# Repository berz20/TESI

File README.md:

# NV Center vectorial magnetometry Analysis

<br />

Git repository for ODMR data analysis done with confocal microscope, applied on NV centers.

<br />

# Contents

- [**How to start**](#contacts)
- [**Brief description**](#course-program)

<br />
<!--------------------------------------------------------------------->

# How to start

In order to make fitting usable, due to the necessity of using lorentzians functions with negative area, the lmfit.models and lmfit.lineshapes files have been modified adding
invlorentzian to lineshapes and the class InvLorentzianModel to models. Surely this is not an elegant neither smart way to do it, but is the only one that has worked stably.

- Search for the files that should be in your python3.10/site-packages/lmfit (on Linux it's sited in ~/.local/lib)
- Either copy the two files for github repository/startup or modify them by adding the modules (Reccomended way)

<br />
<!--------------------------------------------------------------------->

# Brief description

Directories (really messy):

- data
  - Contains data from lab experiences, dir ODMR contains all sets
- docs
  - Abstract and some useful pdfs
- output
  - Contains all txt files filled with the printed output of every run and in dir img all the images created with file src/find_peak_final.py
- presentation
  - Contains all svg files created with Inkscape and slides
- src_EB
  - variables.py : self explanatory
  - functions.py : self explanatory
  - fit_peak_final.py : find peaks, fits with a InvLorentzianModel (with few changes could be implemented for using Gaussians, Lorentzians and Voigt)
  - test_rotative_vectors.py : (only for 8 peaks spectrums) find peaks, fits, plots multiple, plots peaks points and fits with model from hamiltonians.py evaluating possible angle for axis
  - multiple_vector.py : same left graph but 3d plotting of possible vectors
- usb
  - data from lab
  <br />
  <!--------------------------------------------------------------------->

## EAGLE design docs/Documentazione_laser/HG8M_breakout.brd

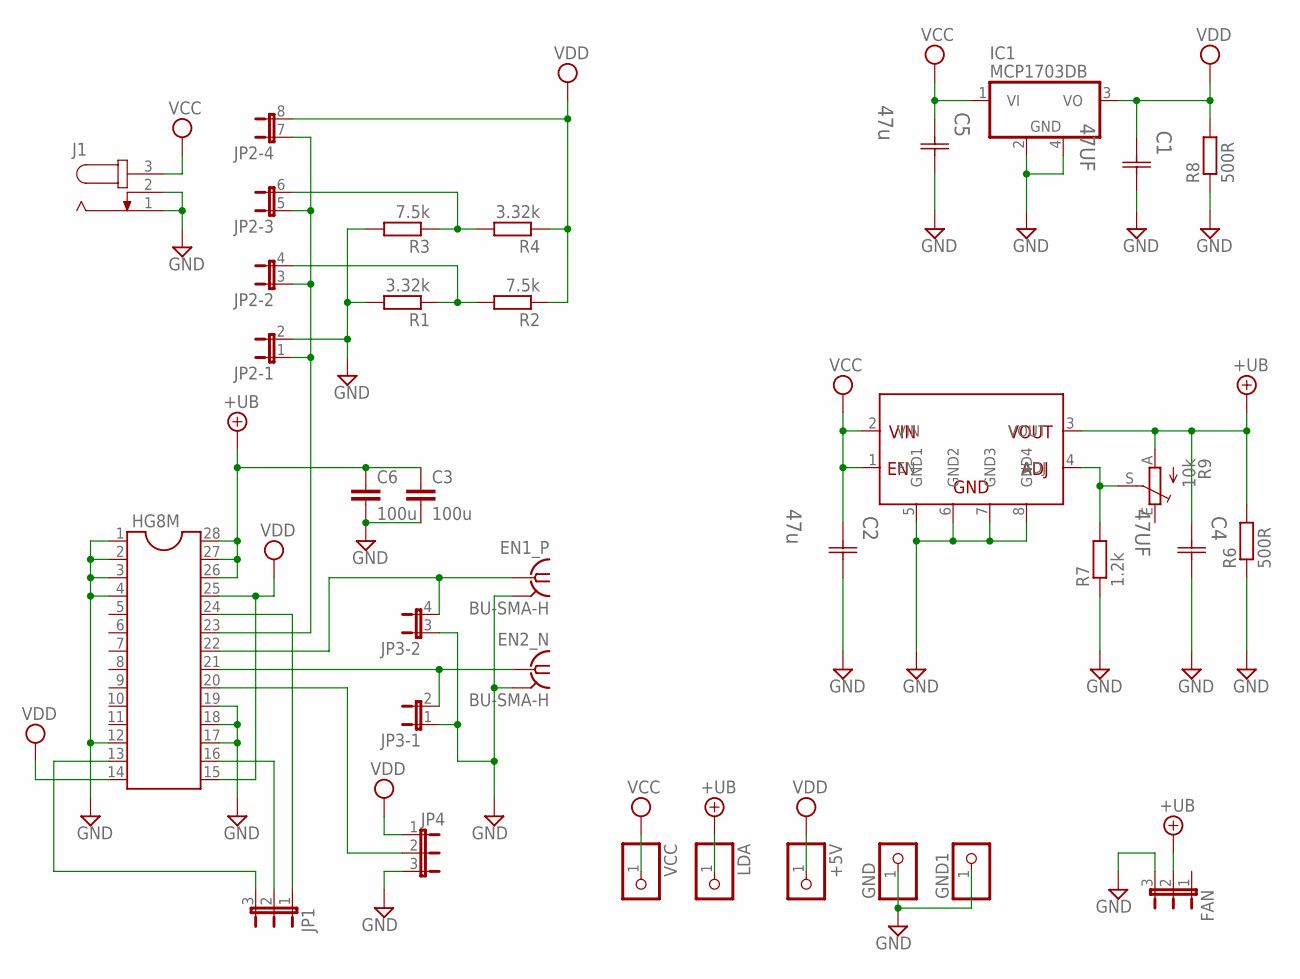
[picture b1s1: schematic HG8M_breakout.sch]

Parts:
+5V: PINHD-1X1; 1X01
C1, C4: 47UF; CAPCP6032X280N
C2, C5: 47u; CAPC3225X94N
C3, C6: 100u; C1210
EN1_P, EN2_N: BU-SMA-H
FAN: JP2E; JP2
GND, GND1: PINHD-1X1; 1X01
HG8M: DIL28; DIL28-6
IC1: MCP1703DB; SOT223
J1: JACK-PLUG1; SPC4078
JP1, JP4: JP2E; JP2
JP2: JP4QE; JP4Q
JP3: JP2QE; JP2Q
LDA: PINHD-1X1; 1X01
R1, R4: 3.32k; R0805
R2, R3: 7.5k; R0805
R6, R8: 500R; R0805
R7: 1.2k; R0805
R9: 10k; B64W
U$4: MIC39102; SOIC8
VCC: PINHD-1X1; 1X01

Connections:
+UB: C3.1, C4.1 (C1), C6.1, FAN.2, HG8M.26, HG8M.27, HG8M.28, LDA.1, R6.2, R9.A, U$4.3 (VOUT)
GND: C1.2 (C2), C2.2 (C2), C3.2, C4.2 (C2), C5.2 (C2), C6.2, EN1_P.2, EN1_P.3 (2), EN1_P.4 (2), EN1_P.5 (2), EN2_N.2, EN2_N.3 (2), EN2_N.4 (2), EN2_N.5 (2), FAN.3, GND.1, GND1.1, HG8M.1, HG8M.2, HG8M.3, HG8M.4, HG8M.12, HG8M.17, HG8M.18, HG8M.19, IC1.2 (GND), IC1.4 (TAP), J1.1, J1.2, JP2.2, JP3.1, JP3.3 (1), JP4.3, R1.2, R3.2, R6.1, R7.1, R8.1, U$4.5 (GND1), U$4.6 (GND2), U$4.7 (GND3), U$4.8 (GND4)
unnamed: EN1_P.1, HG8M.22, JP3.4 (2)
unnamed: EN2_N.1, HG8M.21, JP3.2
unnamed: HG8M.24, JP1.1
unnamed: HG8M.16, JP1.2
unnamed: R7.2, R9.S, U$4.4 (ADJ)
unnamed: HG8M.13, JP1.3
unnamed: HG8M.23, JP2.1, JP2.3 (1), JP2.5 (1), JP2.7 (1)
unnamed: JP2.4 (2), R1.1, R2.2
unnamed: JP2.6 (2), R3.1, R4.2
unnamed: HG8M.20, JP4.2
VCC: C2.1 (C1), C5.1 (C1), IC1.1 (VI), J1.3, U$4.1 (EN), U$4.2 (VIN), VCC.1
VDD: +5V.1, C1.1 (C1), HG8M.14, HG8M.15, HG8M.25, IC1.3 (VO), JP2.8 (2), JP4.1, R2.1, R4.1, R8.2

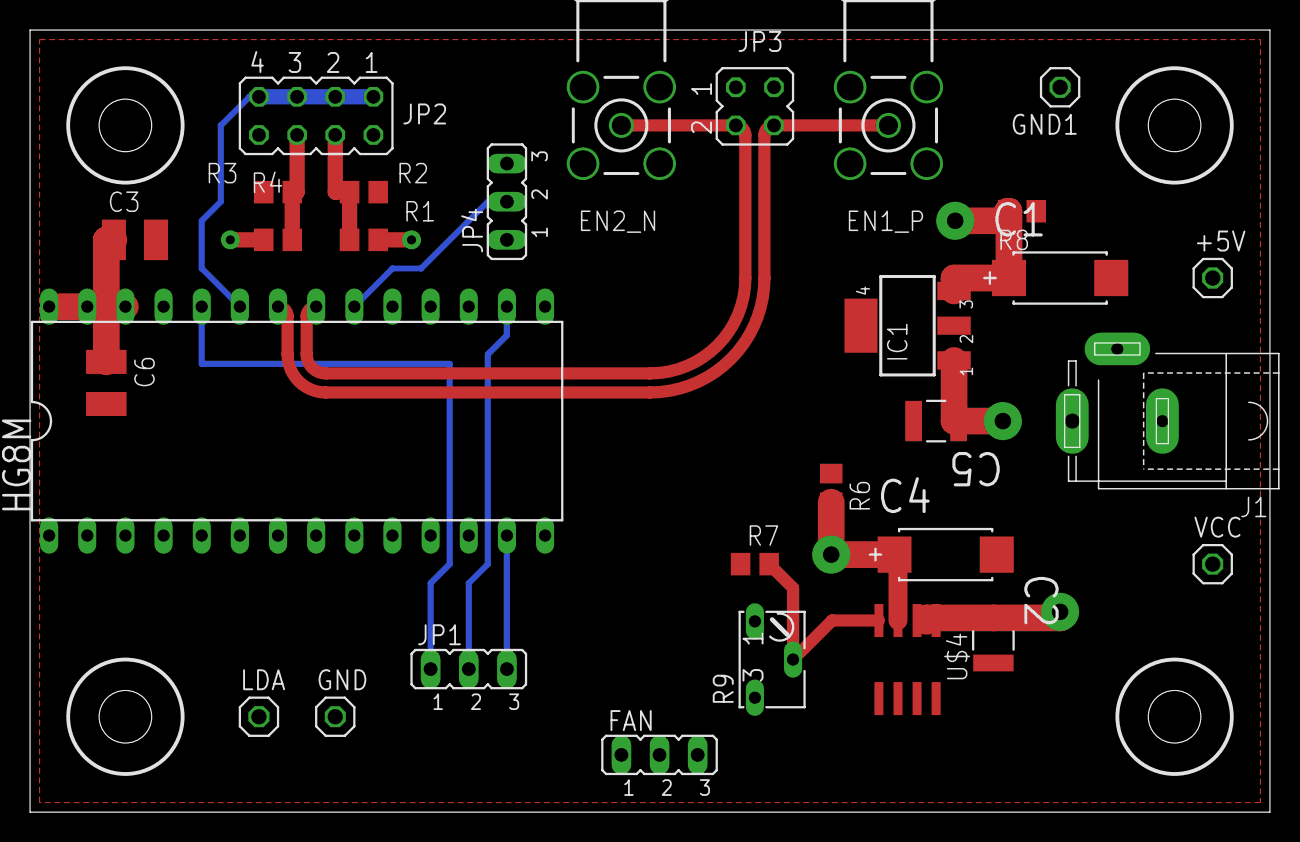
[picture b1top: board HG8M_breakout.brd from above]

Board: 2 copper layers, 82.5 x 52.1 mm, 34 parts (0 on the bottom side), 14 nets.

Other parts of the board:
U$1, U$2, U$3, U$5: DRIL-3,5

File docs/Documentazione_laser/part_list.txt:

Qty.	Part no.			Description

1		MIC39102			Micrel 1A adjustable LDO SMD SOIC-8
1		lm2940				Texas Instruments 1A 5V fixed LDO SMD SOT-223
3							2.54mm 1x3-pol pins
1							2.54mm 2x2-pol pins
1							2.54mm 2x4-pol pins
1		FC681465			DC socket 2.1/2.5mm
1		T93YB				10kOhm 10% tolerance trimmer
2		CRCW08057k50		7.5kOhm resistor SMD 0805
1		CRCW08051k20		1.2kOhm resistor SMD 0805
2		MC01W080513k32		3.32kOhm resistor SMD 0805
2		ERJP06F4990V		499Ohm resistor SMD 0805 0.5W
2		TR3C476K016C0350	47muF 16V tantalum capacitor SMD 6032-28
2		GRM32EC81C476KE15L	47muF 16V ceramic capacitor MLCC SMD 1210
1-2		EMK325ABJ107MM-T	100muF 16V ceramic capacitor MLCC SMD 1210
2		132134				SMA straight PCB jack, through hole, 50Ohm
1		iC-HG iCSY HG8M		demo module DIL28 for iC-HG 3A Laser Switch
1		DIL-28				28 pol DIL28 socket for ICs
1		S7060R 				Thorlabs laser diode socket for 5.6mm package

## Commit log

2022-08-20 commit TESI
2022-08-20 upload foto
2022-08-25 upload foto finale
2022-08-30 double deviation center
2022-08-31 multiple vector analisys
2022-09-01 anglee deviation
2022-09-01 prova deg
2022-09-01 angle deviation
2022-09-05 rotative versors and right angle vector graph
2022-09-07 abstract double
2022-09-11 presentation
2022-09-13 right multiple_vector
2022-09-16 presentation half
2022-09-18 pres + compare Hall
2022-09-23 pres impress + right vector & dev
2022-09-25 presentation odp
2022-10-14 pdf presentation
2022-10-21 pdf introduction
2022-10-22 pdf fonti
2022-10-25 pdf add eigenvalue
2022-11-29 src_EB
2023-04-09 Upload for EB
2023-04-09 Upload first lab
